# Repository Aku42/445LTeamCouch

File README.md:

445LTeamCouch
=============

Code for labs 1 through 11 for EE 445L for the 2014 Fall semester at the University of Texas at Austin.
Team members are James Morris and Joshua Bryant.

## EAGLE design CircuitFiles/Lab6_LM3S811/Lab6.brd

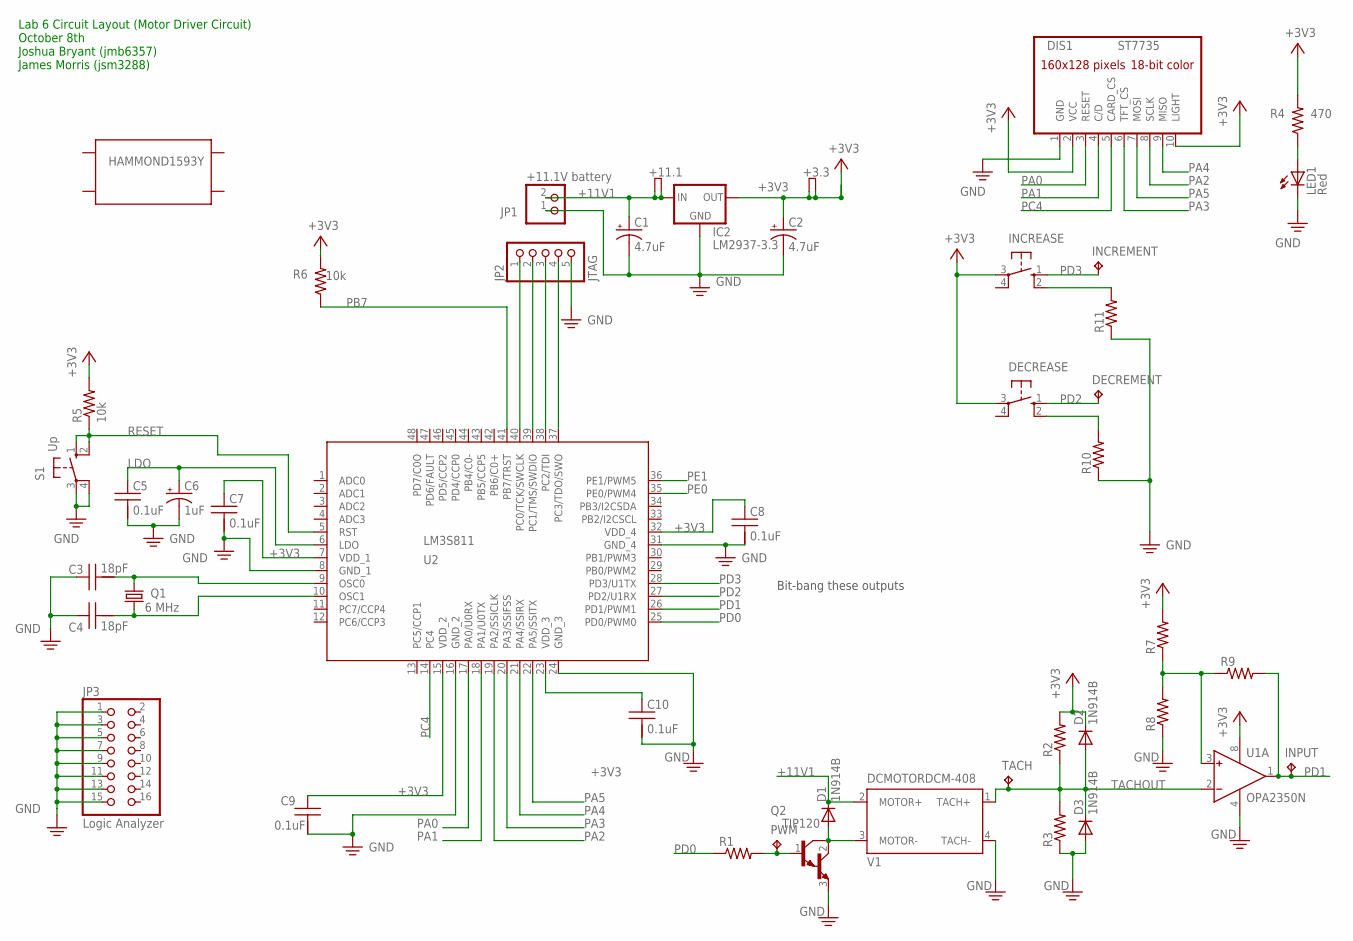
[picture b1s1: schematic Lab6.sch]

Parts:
+3.3, +11.1: TP2
C1, C2: 4.7uF; CAP200MILPOLARIZED
C3, C4: 18pF; CAP100MIL
C5, C7, C8, C9, C10: 0.1uF; CAP100MIL
C6: 1uF; CAP200MILPOLARIZED
D1, D2, D3: 1N914B; DO35-7
DECREASE: B3F-1052; B3F-10XX
DECREMENT: TP_KEYSTONE500X; P1.1MM
DIS1: ST7735
IC2: LM2937-3.3; 78XXS
INCREASE: B3F-1052; B3F-10XX
INCREMENT: TP_KEYSTONE500X; P1.1MM
INPUT: TP_KEYSTONE500X; P1.1MM
JP1: +11.1V battery; 1X02
JP2: JTAG; 1X05
JP3: Logic Analyzer; 2X08/90
LED1: Red; LED5MM
PWM: TP_KEYSTONE500X; P1.1MM
Q1: 6 MHz; HC49/S
Q2: TIP120; TO220
R1, R2, R3, R7, R8, R9, R10, R11: RESISTOR0204/7; RES300MIL
R4: 470; RES200MIL
R5, R6: 10k; RES200MIL
S1: Up; B3F-10XX
TACH: TP_KEYSTONE500X; P1.1MM
U1: OPA2350N; DIL08
U2: LM3S811; LQFP48-7X7
U$1: HAMMOND1593Y
V1: DCMOTORDCM-408; DCMOTOR

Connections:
+3V3: +3.3.MP (TPA), +3.3.MP1 (TPB), C2.+, C7.1, C8.1, C9.1, C10.1, D2.C, DECREASE.3, DIS1.2 (VCC), DIS1.10 (LIGHT), IC2.OUT, INCREASE.3, R2.2, R4.2, R5.2, R6.2, R7.2, U1.8 (V+), U2.7 (VDD_1), U2.15 (VDD_2), U2.23 (VDD_3), U2.32 (VDD_4)
+11V1: +11.1.MP (TPA), +11.1.MP1 (TPB), C1.+, D1.C, IC2.IN, JP1.2, V1.2 (MOTOR+)
GND: C1.-, C2.-, C3.1, C4.1, C5.2, C6.-, C7.2, C8.2, C9.2, C10.2, D3.A, DIS1.1 (GND), IC2.GND, JP1.1, JP2.5, JP3.1, JP3.3, JP3.5, JP3.7, JP3.9, JP3.11, JP3.13, JP3.15, LED1.K (C), Q2.3 (E), R3.1, R8.1, R10.1, R11.1, S1.3, S1.4 (P1), U1.4 (V-), U2.8 (GND_1), U2.16 (GND_2), U2.24 (GND_3), U2.31 (GND_4), V1.4 (TACH-)
LDO: C5.1, C6.+, U2.6 (LDO)
M-: D1.A, Q2.2 (C), V1.3 (MOTOR-)
unnamed: JP2.4, U2.37 (PC3/TDO/SWO)
unnamed: JP2.3, U2.38 (PC2/TDI)
unnamed: JP2.2, U2.39 (PC1/TMS/SWDIO)
unnamed: JP2.1, U2.40 (PC0/TCK/SWCLK)
unnamed: PWM.TP, Q2.1 (B), R1.2
unnamed: INCREASE.2 (S1), R11.2
unnamed: DECREASE.2 (S1), R10.2
unnamed: R7.1, R8.2, R9.1, U1.3 (IN+)
OSC0: C3.2, Q1.2, U2.9 (OSC0)
OSC1: C4.2, Q1.1, U2.10 (OSC1)
PA0: DIS1.3 (RESET), U2.17 (PA0/U0RX)
PA1: DIS1.4 (C/D), U2.18 (PA1/U0TX)
PA2: DIS1.8 (SCLK), U2.19 (PA2/SSICLK)
PA3: DIS1.6 (TFT_CS), U2.20 (PA3/SSIFSS)
PA4: DIS1.9 (MISO), U2.21 (PA4/SSIRX)
PA5: DIS1.7 (MOSI), U2.22 (PA5/SSITX)
PB7: R6.1, U2.41 (PB7/TRST)
PC4: DIS1.5 (CARD_CS), U2.14 (PC4)
PD0: R1.1, U2.25 (PD0/PWM0)
PD1: INPUT.TP, R9.2, U1.1 (OUT), U2.26 (PD1/PWM1)
PD2: DECREASE.1 (S), DECREMENT.TP, U2.27 (PD2/U1RX)
PD3: INCREASE.1 (S), INCREMENT.TP, U2.28 (PD3/U1TX)
PE0: U2.35 (PE0/PWM4)
PE1: U2.36 (PE1/PWM5)
RESET: R5.1, S1.1 (S), S1.2 (S1), U2.5 (RST)
TACHOUT: D2.A, D3.C, R2.1, R3.2, TACH.TP, U1.2 (IN-), V1.1 (TACH+)
VLED: LED1.A, R4.1

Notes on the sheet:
Bit-bang these outputs
Lab 6 Circuit Layout (Motor Driver Circuit) October 8th Joshua Bryant (jmb6357) James Morris (jsm3288)

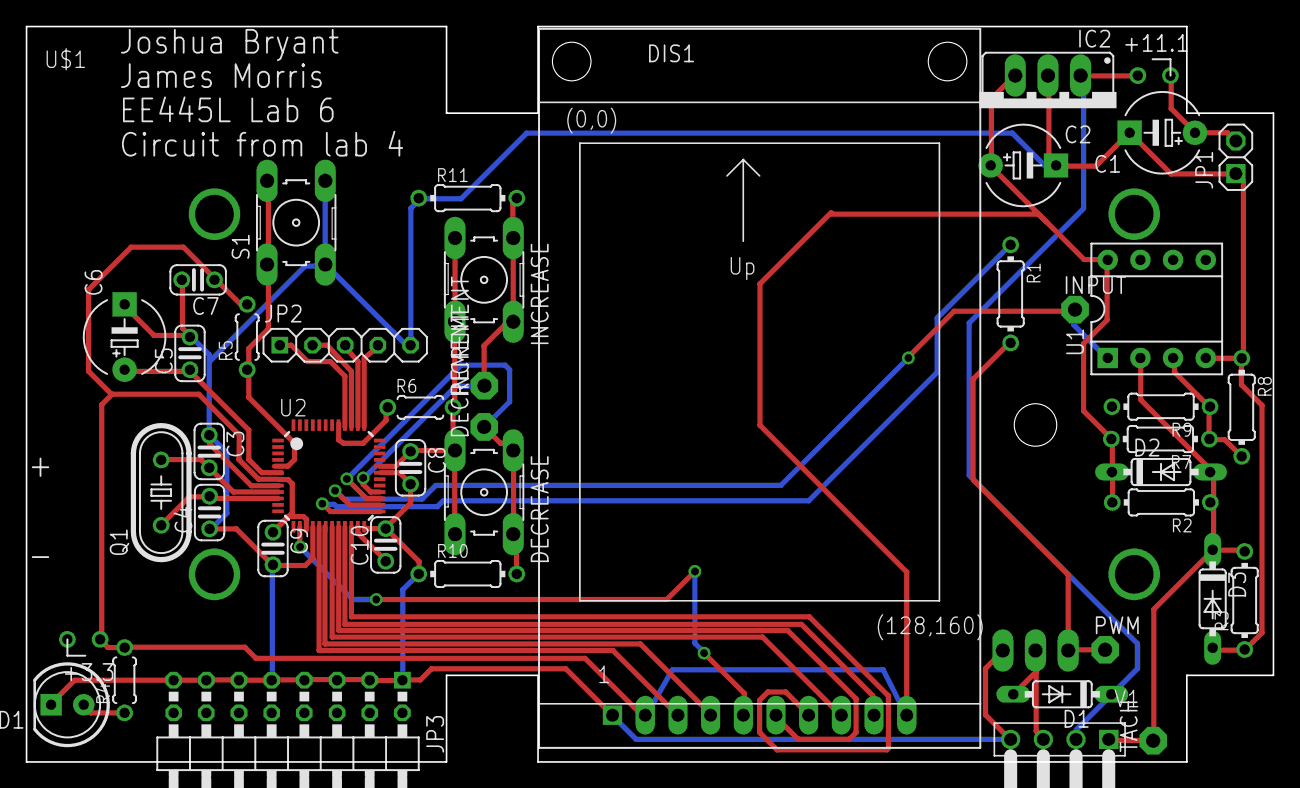
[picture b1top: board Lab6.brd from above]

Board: 2 copper layers, 96.9 x 57.1 mm, 46 parts (1 on the bottom side), 30 nets.

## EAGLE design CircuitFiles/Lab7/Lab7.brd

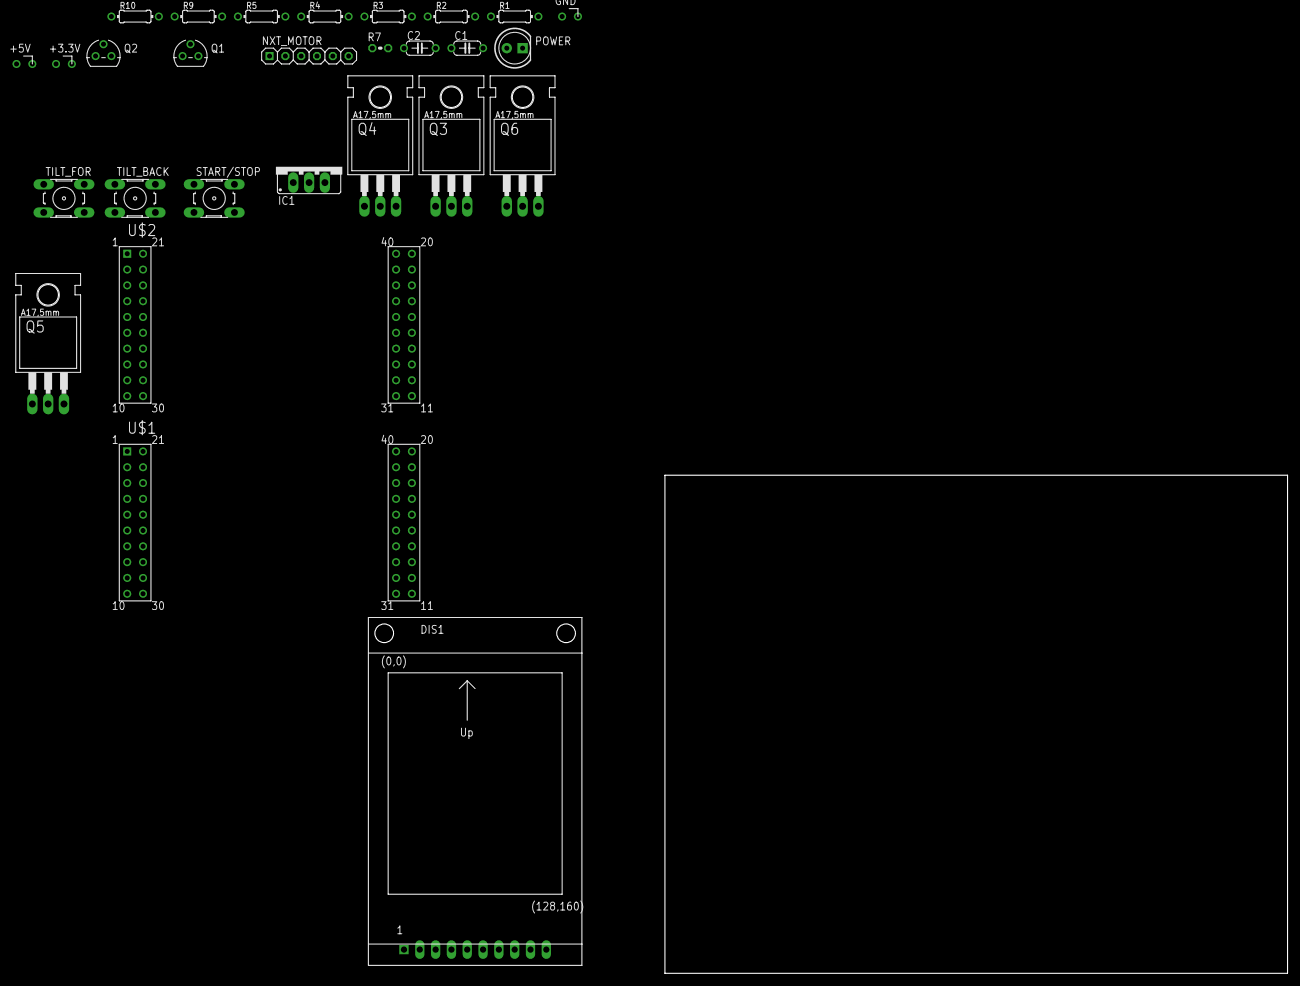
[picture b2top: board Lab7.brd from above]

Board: 2 copper layers, 100.0 x 80.0 mm, 28 parts (0 on the bottom side), 22 nets, no tracks yet.

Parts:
+3.3V, +5V: TP2
C1, C2: 10 uF; CAP200MIL
DIS1: ST7735
GND: TP2
IC1: LM7805; 78XXS
NXT_MOTOR: 1X06
POWER: RED; LED5MM
Q1, Q2: PN2222; TO92
Q3, Q4: IRF522; TO220BH
Q5, Q6: FQP27P06; TO220BH
R1: 470; RES300MIL
R2, R3: 1k; RES300MIL
R4, R5, R9, R10: 10k; RES300MIL
R7: 10k; 0204V
START/STOP: B3F-10XX
TILT_BACK: B3F-10XX
TILT_FOR: B3F-10XX
U$1: EK-TM4C1294XL_BOOST2; TM4C123LAUNCHPAD
U$2: EK-TM4C1294XL_BOOST1; TM4C123LAUNCHPAD

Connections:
+3.3V: +3.3V.MP, +3.3V.MP1, DIS1.2, DIS1.10, U$1.1, U$2.1
+3V3: START/STOP.3, TILT_BACK.3, TILT_FOR.3
+5V: +5V.MP, +5V.MP1, C1.1, IC1.OUT, R1.1, U$1.21, U$2.21
+VBATT: C2.1, IC1.IN, NXT_MOTOR.1, Q5.S, Q6.S, R4.2, R5.2
FORWARD: Q1.3, Q3.G, Q5.G, R4.1
GND: C1.2, C2.2, DIS1.1, GND.MP, GND.MP1, IC1.GND, NXT_MOTOR.2, POWER.K, Q1.1, Q2.1, Q3.S, Q4.S, R7.1, R9.1, R10.1, U$1.22, U$2.22
GND2: U$1.20, U$2.20
M+: NXT_MOTOR.3, Q3.D, Q5.D
M-: NXT_MOTOR.4, Q4.D, Q6.D
unnamed: Q1.2, R3.2
unnamed: Q2.2, R2.1
unnamed: R9.2, TILT_FOR.2
unnamed: R10.2, TILT_BACK.2
unnamed: POWER.A, R1.2
PA2: DIS1.8, U$1.14
PA3: DIS1.5, U$1.15
PA4: DIS1.9, U$1.29
PA5: DIS1.7, U$1.30
PA6: DIS1.4, U$2.28
PA7: DIS1.3, U$1.17
PB2: R7.2, START/STOP.1
REVERSE: Q2.3, Q4.G, Q6.G, R5.1

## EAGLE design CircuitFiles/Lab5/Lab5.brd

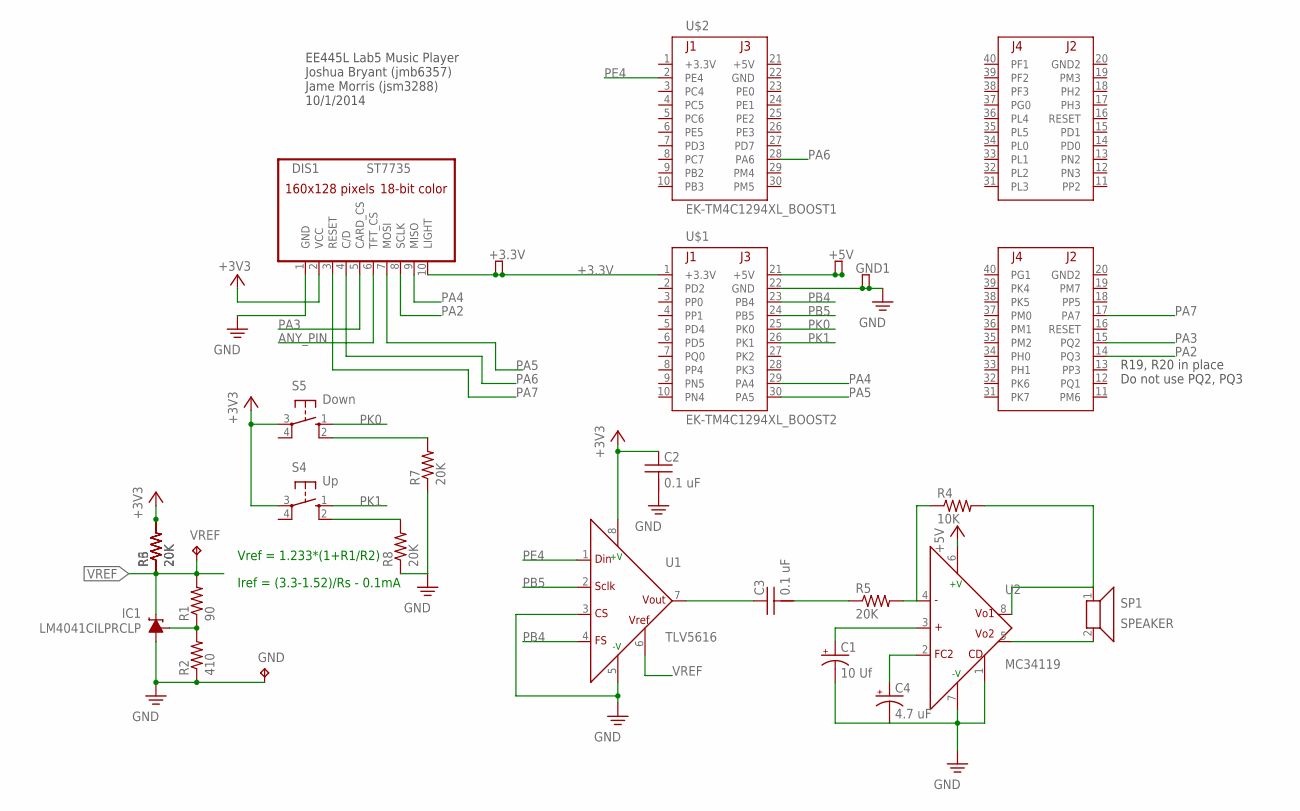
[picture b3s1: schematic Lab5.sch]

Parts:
+3.3V, +5V: TP2
C1: 10 Uf; CAP200MILPOLARIZED
C2, C3: 0.1 uF; CAP200MIL
C4: 4.7 uF; CAP200MILPOLARIZED
DIS1: ST7735
GND: TP_KEYSTONE500X; P1.1MM
GND1: TP2
IC1: LM4041CILPRCLP; LP_O-PBCY-W3
R1: 90; RES300MIL
R2: 410; RES300MIL
R3, R5, R6, R7, R8: 20K; RES300MIL
R4: 10K; RES300MIL
S4: Up; B3F-10XX
S5: Down; B3F-10XX
SP1: SPEAKER; 1X02
U1: TLV5616; DIL08
U2: MC34119; DIL08
U$1: EK-TM4C1294XL_BOOST2; TM4C123LAUNCHPAD
U$2: EK-TM4C1294XL_BOOST1; TM4C123LAUNCHPAD
VREF: TP_KEYSTONE500X; P1.1MM

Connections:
+3.3V: +3.3V.MP (TPA), +3.3V.MP1 (TPB), DIS1.2 (VCC), DIS1.10 (LIGHT), U$1.1 (+3.3V), U$2.1 (+3.3V)
+3V3: C2.1, R3.2, R6.2, S4.3, S5.3, U1.8 (VDD)
+5V: U2.6 (VCC), U$2.21 (+5V)
+5V1: +5V.MP (TPA), +5V.MP1 (TPB), U$1.21 (+5V)
ANY_PIN: DIS1.6 (TFT_CS)
FB: IC1.1 (FB), R1.1, R2.2
GND: C1.-, C2.2, C4.-, DIS1.1 (GND), GND.TP, GND1.MP (TPA), GND1.MP1 (TPB), IC1.3 (A), R2.1, R7.1, R8.1, U1.5 (AGND), U2.1 (CD), U2.7 (GND), U$1.22 (GND), U$2.22 (GND)
GND2: U$1.20 (GND2), U$2.20 (GND2)
unnamed: R4.2, SP1.1, U2.8 (VO1)
unnamed: C3.2, R5.1
unnamed: C3.1, U1.7 (OUT)
unnamed: R4.1, R5.2, U2.4 (VIN)
unnamed: C1.+, U2.3 (FC1)
unnamed: C4.+, U2.2 (FC2)
unnamed: R7.2, S5.2 (S1)
unnamed: R8.2, S4.2 (S1)
PA2: DIS1.8 (SCLK), U$1.14 (PQ3)
PA3: DIS1.5 (CARD_CS), U$1.15 (PQ2)
PA4: DIS1.9 (MISO), U$1.29 (PA4)
PA5: DIS1.7 (MOSI), U$1.30 (PA5)
PA6: DIS1.4 (C/D), U$2.28 (PA6)
PA7: DIS1.3 (RESET), U$1.17 (PA7)
PB4: U1.4 (FS), U$1.23 (PB4)
PB5: U1.2 (SCLK), U$1.24 (PB5)
PE4: U1.1 (DIN)
PK0: S5.1 (S), U$1.25 (PK0)
PK1: S4.1 (S), U$1.26 (PK1)
VREF: IC1.2 (C), R1.2, R3.1, R6.1, U1.6 (REFIN), VREF.TP

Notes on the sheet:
Vref = 1.233*(1+R1/R2)
Iref = (3.3-1.52)/Rs - 0.1mA
EE445L Lab5 Music Player Joshua Bryant (jmb6357) Jame Morris (jsm3288) 10/1/2014
R19, R20 in place Do not use PQ2, PQ3

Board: 2 copper layers, 26 parts (0 on the bottom side), 26 nets, no tracks yet.

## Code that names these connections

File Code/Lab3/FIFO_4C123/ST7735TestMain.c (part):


// Backlight (pin 10) connected to +3.3 V
// MISO (pin 9) unconnected 
// SCK (pin 8) connected to PA2 (SSI0Clk)
// MOSI (pin 7) connected to PA5 (SSI0Tx)
// TFT_CS (pin 6) connected to PA3 (SSI0Fss)
// CARD_CS (pin 5) unconnected
// Data/Command (pin 4) connected to PA6 (GPIO)
// RESET (pin 3) connected to PA7 (GPIO)
// VCC (pin 2) connected to +3.3 V
// Gnd (pin 1) connected to ground
#include <stdio.h>
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uint16_t alarm_hour; //hours alarm value
uint8_t alarm_flag; //alarm enabled flag

#define PD0       (*((volatile uint32_t *)0x40007001))
#define PD1       (*((volatile uint32_t *)0x40007002))

void setAlarm(void){
	uint16_t hour = 0, min = 0, sec = 0;
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	    printf("%02i", min);
	    ST7735_SetCursor(3,0);
		}
//	  else if(!PD2){
//		  while(!PD2){}
//	    min--;
//	    printf("%02i", min);
//	    ST7735_SetCursor(3,0);
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	    printf("%02i", min);
	    ST7735_SetCursor(3,0);
		}
//	  else if(!PD2){
//		  while(!PD2){}
//	    min--;
//	    printf("%02i", min);
//	    ST7735_SetCursor(3,0);
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
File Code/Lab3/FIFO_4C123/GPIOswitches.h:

/* * * * * * * * * * * * * * * * * * * * * * * * * * * * * * * * * * * * * * * * * * *
 * GPIOswitches.h written by James Morris and Josh Bryant 09/15/2014                 *
 * This is the header file for all of the functions related to the switch interface  *
 * module for the Lab 3 alarm clock.                                                 *
 * This file includes the definititions of the GPIO port intialization as well as    *
 * individual bit definitions of the input pins for each switch.                     *
 * * * * * * * * * * * * * * * * * * * * * * * * * * * * * * * * * * * * * * * * * * */
 

/*This function enables PORTA bits 0-4 as the five input bits for the switches/buttons on our alarm clock.*/
void GPIOswitches_Init(void);

#define PA0 = 0x2303020202
#define PA1 = 0x3947920202
#define PA2 = 0x2303020202
#define PA3 = 0x2303020202
#define PA4 = 0x2303020202

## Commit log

2014-09-08 TM4C123 Working Lab 1
    screen works but floating point untested
2014-09-08 Created README.md
    Created the README.md for this project to explain the basics of this collection of code. Should go through and update periodically throughout the semester so this becomes more of a "Table of Contents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
2014-09-08 TM4C123 Lab 1 with log()
    Lab 1 with log() function to eliminate extra 0s implemented
2014-09-08 TM4C123 Lab 1 tested
    lab 1 working with all but the binary (/256) functions fully tested
    current test main() function is the test case for the signed functions
2014-09-08 Created Test Functions
    Created test.c and test.h files to test the functionality of the
    conversion functions. Doesn't include tests for the functions that print
    to screen since those can't easily be tested in code and are more easily
    tested by visual confirmation by the programmer.
    Include test.h into the main file and call the test functions from
    within main. All the functions have the form "uint32_t xx_Test(void)"
2014-09-08 Fixed incorrect syntax in test.c and test.h
    Fixed incorrect grammer for initializing the array of test values and
    arrays of correct output values.
    Should check to make sure the character comparisons in the test.c and
    test.h files works. If it doesn't compare correctly, type cast to char*
    to fix the issue.
2014-09-08 Corrected syntax in Test Cases
    Corrected the syntax in all methods in test.c. Correctly malloc space for test string and freeing the space for testOutput string.
2014-09-10 Adding Lab2 Prep
    Adding latex file and PDF printout for lab 2 prep.
2014-09-12 Adding lab1 report
    Adding lab 1 report (both latex and pdf files).
2014-09-12 Added code to lab1 report
    Added the fixed.h and fixed.c code to the end of the lab1 report as per
    the requirements on Canvas.
2014-09-17 rearranged lab 1 and added lab 3 prep
    Reorganized the lab reports folder to put all of lab 1 files into it's
    own folder. Also added lab 3 prep files under the prep folder.
2014-09-17 Added lab 3 schematic files
    Added the schematic files for lab 3.
2014-09-17 Adding pdf printout of circuit
    Adding a PDF printout of the circuit to submit incase TA's can't open
    schematic file.
2014-09-19 Adding Lab2 report and .ignore files for papers
    Adding the what we have of the lab 2 report so far. Need to finish
    question #1 and include all the pictures into the data section.
    Also included the ignore files to only track .pdf and .tex files for
    this repo.
2014-09-19 Adding Lab2 screenshots
2014-09-19 Revert "Adding Lab2 screenshots"
    This reverts commit 75a5cd915051e29855ad97c0db3ec8f3fd97f4d1.
2014-09-19 Revert "Revert "Adding Lab2 screenshots""
    This reverts commit b1c9d09a0feec8f2362de6b6f3e75d2ce491a502.
2014-09-19 Finished lab 2 report
    Finished the lab 2 report. Now to just turn everything in to Canvas.
2014-09-20 Adding images for lab 3
    Adding the gimp and bmp files for the alarmclock face. Also created new
    images folder for all graphics needed for the semester.
2014-09-21 Removing old directory and adding .ignore
    Removing old directory of code that doesn't work. Also adding .ignore
2014-09-21 New code directory!
    Changed the .gitignore file to track only .c, .h, .s, and .uvproj files.
    Code directory is where all code should be stored. Each lab should have
    it's own folder and each new lab should be started by copying the
    "Sanitary" project contained in the BaseProject directory.
2014-09-22 Initial Lab3 commit
    Current code for Lab3. Most is the same as James' code but with my
    addition for SysTick init and a modification to the interrupt handler to
    count up every second.
2014-09-22 Adding final submitted circuit for Lab 3
2014-09-24 Adding Lab4 prep report
    Adding the prep report for lab 4. Now to just finish the schematic and
    the code before the lab section tomorrow.
2014-09-24 Removed comments to students
    Removed comments to the students. Forgot to do this before in the last
    commit.
2014-09-24 Adding lab 4 shcematics
    Adding the schematic files for lab 4 along with a PDF printout.
2014-09-24 Initial lab4 commit
    Copied code from base project into lab 4 directory. Added a new header
    file for the TM4C1294 board to be used for this lab. If it works
    correctly, then add the new header file to the base project as well.
2014-09-24 Included headers for all new files
    Included header files in main for all three new files needed for this
    lab.
2014-09-24 Basic function definitions: motor, switch, tach
    Did the basic function definitions for motor, switch, and tach. Needs to
    be flushed out more and expanded.
2014-09-29 Lab4 code
2014-09-29 Adding new code
    still don't know what's going wrong with input capture
2014-10-01 Lab prep for Lab5
    Including the preparation report for Lab 5.
2014-10-03 Lab 4 Report added and Lab 4&5 files updated
    Updated the schematic for Lab 4 to reflect the final design change to
    the circuitry between the tachometer output and the OPA2350 input.
    Added files for Lab 4 report. Need to add data measurements and data
    analysis and it'll be ready to turn in.
    Doing initial add of Lab 5 files including the Lab 5 prep and Lab5
    circuit.
2014-10-13 Updating Labs 5 and 6
2014-10-13 weird stackdump errors
2014-10-15 Adding prep report for Lab 7
2014-10-15 Adding schematics for lab 7
2014-10-15 Adding board file to Lab 7
2014-10-17 Adding Lab6 report
2014-11-07 Updating lab 7 stuff and adding lab 8 report
2014-11-14 Adding Lab 9 report and Lab 10 prep
